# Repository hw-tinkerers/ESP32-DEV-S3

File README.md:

# ESP32-S3_Dev_Board
This development board is based on ESP32-S3 chipset which is aimed to solve the problem having to carry multiple tools to debug and capture data on RS485 and CAN bus.

<strong> Front view (Rendering)</strong>

<strong> Back view (Rendering)</strong>

The board is capable of operating in multiple modes.
1. With Firmware support (Still in making):
    1. CAN bus Decoder
    2. RS485 Decoder 

2. Standalone Hardware support:
    1. RS485 to USB converter
    2. USB to UART converter

3. Normal Development baord for ESP32-S3 Development.

<strong>The Board supports a wide variety of features.</strong>

| Interface    | Controller | Driver/Component |
| -------- | ------- | ------- |
| UART | on-chip | serial port |
GPIO | on-chip | gpio |
PINMUX | on-chip | pinmux |
USB-JTAG | on-chip | hardware interface
SPI Master | on-chip | spi
TWAI/CAN controller | on-chip | can
ADC | on-chip | adc
Timers | on-chip | counter
Watchdog | on-chip | watchdog	
TRNG | on-chip | entropy
MCPWM | on-chip | pwm 
PCNT | on-chip | qdec
GDMA | on-chip | dma
LEDC | on-chip | pwm
CAN trasnceiver | on-board | can
RS485 transceiver | on-board | serial-port
UART-to-USB | on-board | Hardare based

<strong>Development enviroinment support </strong>
The board is designed keeping open-source support in mind.
The main motive is to provide support on multiple development environments to cater to different people ranging from begginers to professionls. 

The supported platforms are listed below

1. Arduino IDE
2. ESP-IDF
3. Zephyr-RTOS

The guide on getting started on each platform is still in making. Stay tuned for further updates.

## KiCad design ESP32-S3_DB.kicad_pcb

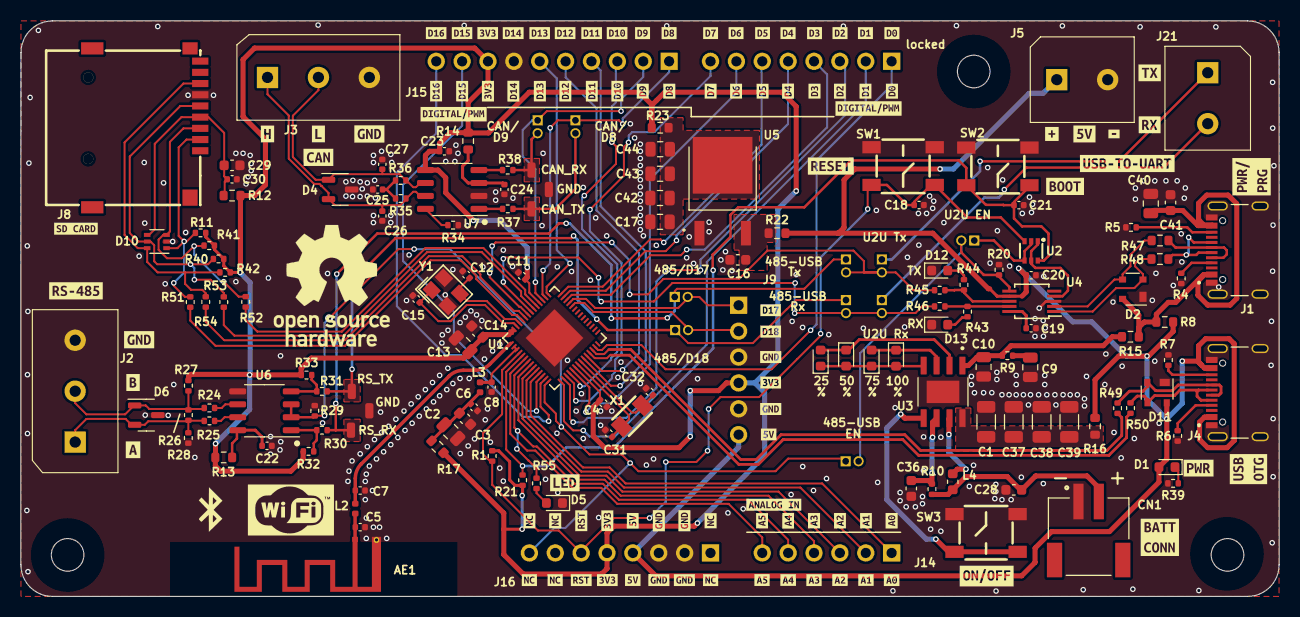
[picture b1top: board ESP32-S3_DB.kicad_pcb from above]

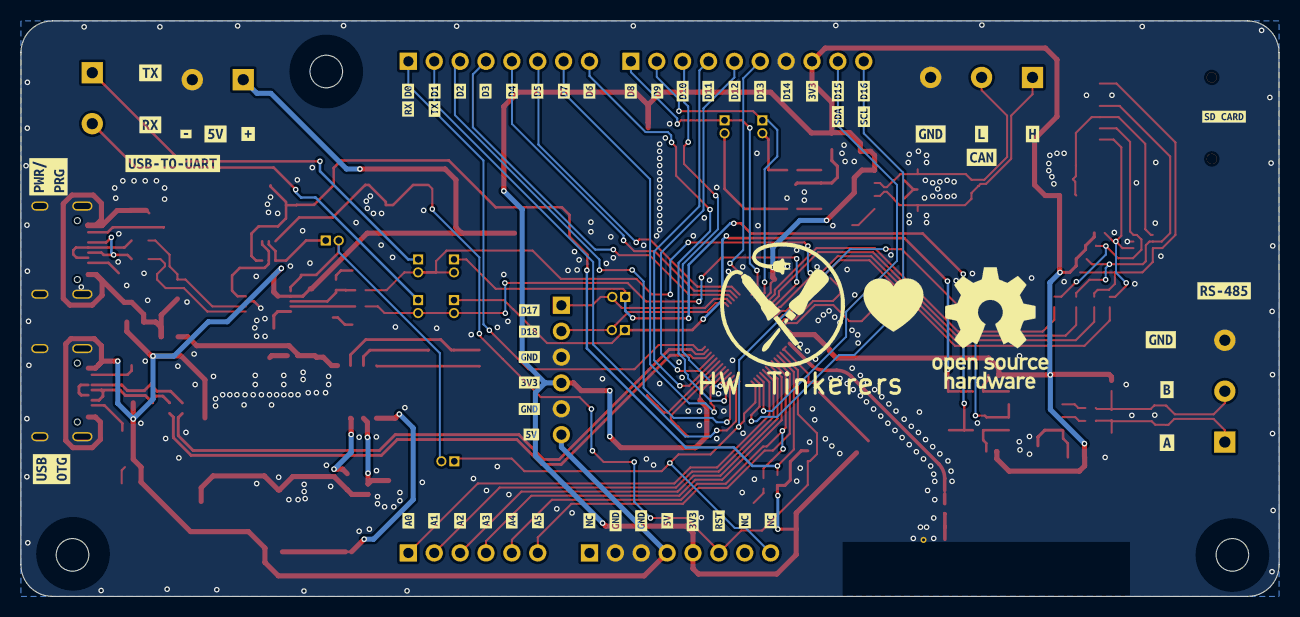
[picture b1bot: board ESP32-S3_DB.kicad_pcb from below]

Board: 4 copper layers, 123.5 x 56.5 mm, 310 parts (60 on the bottom side), 104 nets.

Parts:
AE1: Antenna_Shield; BLE_ANTENNA
C1, C37, C38, C39: 22uF; C_1206_3216Metric
C2, C9, C10, C13, C17, C40, C42, C43, C44: 10uF; C_0805_2012Metric
C3, C14, C16, C29, C41: 1uF; C_0603_1608Metric
C4, C6, C8, C11, C18, C19, C20, C21, C22, C23, C24, C30: 100nF; C_0402_1005Metric
C5, C7: 3.3pF; C_0402_1005Metric
C12, C15, C31, C32: 15pF; C_0402_1005Metric
C25, C26, C27: 10nF; C_0402_1005Metric
C28, C36: 22uF; C_0603_1608Metric
CN1: JST_Battery; JST_2mm
D1: BLUE; LED_0603_1608Metric
D2, D11: PRTR5V0U2X; SOT-143
D3, D5, D7, D8, D9, D12, D13: GREEN; LED_0603_1608Metric
D4: PESD2CAN; SOT-23-3
D6: SM712_C293966; SOT-23-3
D10: PESD3V3L5UY,115; SOT-363_SC-70-6
H1, H2, H3: MountingHole; MountingHole_3.2mm_M3
J1, J4: TYPE-C-31-M12_13; tyye_c_connector
J2: A - B; 3P_Screw_Terminal
J3: H - L; 3P_Screw_Terminal
J5: EXT_LOAD; 2P_Screw_Terminal
J6: R4_TX; PinHeader_1x02_P1.27mm_Vertical
J7: R4_RX; PinHeader_1x02_P1.27mm_Vertical
J8: Micro_SD_Card_Det1; TF-SMD_TF-012
J9, J14: Conn_01x06; PinHeader_1x06_P2.54mm_Vertical
J10: U2RS485_TX; PinHeader_1x02_P1.27mm_Vertical
J11: CAN_TX; PinHeader_1x02_P1.27mm_Vertical
J12: CAN_RX; PinHeader_1x02_P1.27mm_Vertical
J15: Conn_01x10; PinHeader_1x10_P2.54mm_Vertical
J16: Conn_01x08; PinHeader_1x08_P2.54mm_Vertical
J17: U2RS485_RX; PinHeader_1x02_P1.27mm_Vertical
J18: U2RS485_DE_~{RE}; PinHeader_1x02_P1.27mm_Vertical
J19: U2U_TX; PinHeader_1x02_P1.27mm_Vertical
J20: U2U_RX; PinHeader_1x02_P1.27mm_Vertical
J21: U2U; 2P_Screw_Terminal
J22: PROG_Default; PinHeader_1x02_P1.27mm_Vertical
L2, L3: 2.2nH; L_0402_1005Metric
L4: 1uH; L_0603_1608Metric
R1, R11, R21, R27, R28, R29, R40, R41, R42: 10k; R_0402_1005Metric
R4, R5, R6, R7, R20, R32, R33, R34: 5k1; R_0402_1005Metric
R8, R12, R13, R14, R15, R16, R17, R22, R23, R47, R48: 0E; R_0603_1608Metric
R9: 2E; R_0402_1005Metric
R10: 0.5E; R_0402_1005Metric
R24, R25, R30, R31, R37, R38, R45, R46, R49, R50, R51, R52, R53, R54: 10E; R_0402_1005Metric
R26: 120E; R_0402_1005Metric
R35: 59E; R_0402_1005Metric
R36: 59; R_0402_1005Metric
R39, R43, R44, R55: 500; R_0402_1005Metric
SW1: RESET; KEY-SMD_4P-L5.2-W5.2-P3.70-LS6.4
SW2: BOOT; KEY-SMD_4P-L5.2-W5.2-P3.70-LS6.4
SW3: ON/OFF; KEY-SMD_4P-L5.2-W5.2-P3.70-LS6.4
SYM1, SYM2: Logo_Open_Hardware_Large; OSHW-Logo_11.4x12mm_SilkScreen
TP1: RS_RX; Test_Pad_1.5mm
TP2: RS_TX; Test_Pad_1.5mm
TP3: CAN_TX; Test_Pad_1.5mm
TP4: CAN_RX; Test_Pad_1.5mm
TP5, TP6: GND; Test_Pad_1.5mm
U1: ESP32-S3FH4R2; QFN-56_L7.0-W7.0-P0.40-TL-EP4.0
U2: UMH3N; SC-70-6_L2.2-W1.3-P0.65-LS2.1-BR
U3: IP5306; ESOP-8
U4: CH340X; MSOP-10_3x3mm_P0.5mm
U5: LD1117DT33CTR; DPAK
U6: SP3071EEN-L/TR; SOP-8_3.9x4.9mm_P1.27mm
U7: ATA6561-GAQW-N; SOP-8_3.9x4.9mm_P1.27mm
X1: 32.768KHz; CRYSTAL-SMD_L3.2-W1.5
Y1: 40MHz; CRYSTAL-SMD_4P-L3.2-W2.5-BL
kibuzzard-65A92C15, kibuzzard-65A92C15#2, kibuzzard-65A92C15#3: G***; kibuzzard-65A92C15
kibuzzard-65A92C32, kibuzzard-65A92C32#2, kibuzzard-65A92C32#3: G***; kibuzzard-65A92C32
kibuzzard-65A92C44, kibuzzard-65A92C44#2, kibuzzard-65A92C44#3: G***; kibuzzard-65A92C44
kibuzzard-65A92C55, kibuzzard-65A92C55#2, kibuzzard-65A92C55#3: G***; kibuzzard-65A92C55
kibuzzard-65A92C85, kibuzzard-65A92C85#2, kibuzzard-65A92C85#3: G***; kibuzzard-65A92C85
kibuzzard-65A92C90, kibuzzard-65A92C90#2, kibuzzard-65A92C90#3: G***; kibuzzard-65A92C90
kibuzzard-65A92C99, kibuzzard-65A92C99#2, kibuzzard-65A92C99#3: G***; kibuzzard-65A92C99
kibuzzard-65A92CA3, kibuzzard-65A92CA3#2, kibuzzard-65A92CA3#3: G***; kibuzzard-65A92CA3
kibuzzard-65A92CE7, kibuzzard-65A92CE7#2: G***; kibuzzard-65A92CE7
kibuzzard-65A92E71, kibuzzard-65A92E71#2: G***; kibuzzard-65A92E71
kibuzzard-65A922D3, kibuzzard-65A922D3#2, kibuzzard-65A922D3#3: G***; kibuzzard-65A922D3
kibuzzard-65A922DA, kibuzzard-65A922DA#2, kibuzzard-65A922DA#3: G***; kibuzzard-65A922DA
kibuzzard-65A922E0, kibuzzard-65A922E0#2, kibuzzard-65A922E0#3: G***; kibuzzard-65A922E0
kibuzzard-65A922F7, kibuzzard-65A922F7#2, kibuzzard-65A922F7#3: G***; kibuzzard-65A922F7
kibuzzard-65A932A3, kibuzzard-65A932A3#2: G***; kibuzzard-65A932A3
kibuzzard-65A932F7, kibuzzard-65A932F7#2: G***; kibuzzard-65A932F7
kibuzzard-65A934AB, kibuzzard-65A934AB#2: G***; kibuzzard-65A934AB
kibuzzard-65A937AF, kibuzzard-65A937AF#2: G***; kibuzzard-65A937AF
kibuzzard-65A937DF: G***; kibuzzard-65A937DF
kibuzzard-65A9230D, kibuzzard-65A9230D#2, kibuzzard-65A9230D#3: G***; kibuzzard-65A9230D
kibuzzard-65A9357B: G***; kibuzzard-65A9357B
kibuzzard-65A9398B, kibuzzard-65A9398B#2: G***; kibuzzard-65A9398B
kibuzzard-65A92320, kibuzzard-65A92320#2, kibuzzard-65A92320#3: G***; kibuzzard-65A92320
kibuzzard-65A92621: G***; kibuzzard-65A92621
kibuzzard-65A93244, kibuzzard-65A93244#2: G***; kibuzzard-65A93244
kibuzzard-65A93266, kibuzzard-65A93266#2: G***; kibuzzard-65A93266
kibuzzard-65A93272, kibuzzard-65A93272#2: G***; kibuzzard-65A93272
kibuzzard-65A93313, kibuzzard-65A93313#2: G***; kibuzzard-65A93313
kibuzzard-65A93322, kibuzzard-65A93322#2: G***; kibuzzard-65A93322
kibuzzard-65A93334, kibuzzard-65A93334#2: G***; kibuzzard-65A93334
kibuzzard-65A93499, kibuzzard-65A93499#2: G***; kibuzzard-65A93499
kibuzzard-65A93960, kibuzzard-65A93960#2: G***; kibuzzard-65A93960
kibuzzard-65AB7A1C: G***; kibuzzard-65AB7A1C
kibuzzard-65AB7A3B, kibuzzard-65AB7A3B#2: G***; kibuzzard-65AB7A3B
kibuzzard-65AB7A4E, kibuzzard-65AB7A4E#2: G***; kibuzzard-65AB7A4E
kibuzzard-65AB7A5E, kibuzzard-65AB7A5E#2: G***; kibuzzard-65AB7A5E
kibuzzard-65AB7A9A, kibuzzard-65AB7A9A#2: G***; kibuzzard-65AB7A9A
kibuzzard-65AB7A9F: G***; kibuzzard-65AB7A9F
kibuzzard-65AB7A26, kibuzzard-65AB7A26#2: G***; kibuzzard-65AB7A26
kibuzzard-65AB7A41: G***; kibuzzard-65AB7A41
kibuzzard-65AB7A48: G***; kibuzzard-65AB7A48
kibuzzard-65AB7A58: G***; kibuzzard-65AB7A58
kibuzzard-65AB7A95: G***; kibuzzard-65AB7A95
kibuzzard-65AB7AA6, kibuzzard-65AB7AA6#2: G***; kibuzzard-65AB7AA6
kibuzzard-65AB7AAC: G***; kibuzzard-65AB7AAC
kibuzzard-65AB7AB4, kibuzzard-65AB7AB4#2: G***; kibuzzard-65AB7AB4
kibuzzard-65AB7ABA: G***; kibuzzard-65AB7ABA
kibuzzard-65AB7AC0, kibuzzard-65AB7AC0#2: G***; kibuzzard-65AB7AC0
kibuzzard-65AB7B50: G***; kibuzzard-65AB7B50
kibuzzard-65AB7B59, kibuzzard-65AB7B59#2: G***; kibuzzard-65AB7B59
kibuzzard-65AB7B60: G***; kibuzzard-65AB7B60
kibuzzard-65AB7B68, kibuzzard-65AB7B68#2: G***; kibuzzard-65AB7B68
kibuzzard-65AB72BB, kibuzzard-65AB72BB#2, kibuzzard-65AB72BB#3: G***; kibuzzard-65AB72BB
kibuzzard-65AB72CF, kibuzzard-65AB72CF#2, kibuzzard-65AB72CF#3: G***; kibuzzard-65AB72CF
kibuzzard-65AB99D3, kibuzzard-65AB99D3#2: G***; kibuzzard-65AB99D3
kibuzzard-65AB729F, kibuzzard-65AB729F#2, kibuzzard-65AB729F#3, kibuzzard-65AB729F#4, kibuzzard-65AB729F#5, kibuzzard-65AB729F#6: G***; kibuzzard-65AB729F
kibuzzard-65AB730A, kibuzzard-65AB730A#2, kibuzzard-65AB730A#3: G***; kibuzzard-65AB730A
kibuzzard-65AB731E, kibuzzard-65AB731E#2, kibuzzard-65AB731E#3, kibuzzard-65AB731E#4, kibuzzard-65AB731E#5, kibuzzard-65AB731E#6: G***; kibuzzard-65AB731E
kibuzzard-65AB7281, kibuzzard-65AB7281#2, kibuzzard-65AB7281#3: G***; kibuzzard-65AB7281
kibuzzard-65ABCD1E, kibuzzard-65ABCD1E#2: G***; kibuzzard-65ABCD1E
kibuzzard-65ABCD6A, kibuzzard-65ABCD6A#2: G***; kibuzzard-65ABCD6A
kibuzzard-65ABCD30, kibuzzard-65ABCD30#2: G***; kibuzzard-65ABCD30
kibuzzard-65ABCD42, kibuzzard-65ABCD42#2, kibuzzard-65ABCD42#3, kibuzzard-65ABCD42#4: G***; kibuzzard-65ABCD42
kibuzzard-65ABCD53, kibuzzard-65ABCD53#2: G***; kibuzzard-65ABCD53
kibuzzard-65ABCFED: G***; kibuzzard-65ABCFED
kibuzzard-65ABD001: G***; kibuzzard-65ABD001
kibuzzard-65ABD06D, kibuzzard-65ABD06D#2: G***; kibuzzard-65ABD06D
kibuzzard-65ABD087, kibuzzard-65ABD087#2: G***; kibuzzard-65ABD087
kibuzzard-65AD136A: G***; kibuzzard-65AD136A
kibuzzard-65AD1381: G***; kibuzzard-65AD1381
kibuzzard-65CC7CB6: G***; kibuzzard-65CC7CB6
kibuzzard-65CC7CF4: G***; kibuzzard-65CC7CF4
kibuzzard-65CDB80D: G***; kibuzzard-65CDB80D
kibuzzard-65CDB868: G***; kibuzzard-65CDB868
locked: Conn_01x08; PinHeader_1x08_P2.54mm_Vertical

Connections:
/3V3: C4.1, C11.1, C13.1, C14.1, C23.1, J9.4, J15.8, J16.5, R1.1, R11.2, R12.1, R13.2, R14.1, R17.1, R21.1, R23.2, R27.2, R32.2, R33.2, R40.2, R41.2, R42.2, U1.20 (VDD3P3_RTC), U1.46 (VDD3P3_CPU), U1.55 (VDDA), U1.56 (VDDA), U7.5 (VIO)
/5V: C20.2, D1.2 (A), D11.4 (VCC), J4.A4 (VBUS), J4.B4 (VBUS), J5.1, J9.6, J16.4, R8.2, R16.2, R22.1, U4.7 (VCC)
/485_TRANS_RX: J7.1, J17.1, R30.1, TP1.1
/485_TRANS_TX: J6.1, J10.1, R31.1, TP2.1
/BOOT: C21.2, R21.2, SW2.2, U1.5 (GPIO0), U2.6
/CAN TRANSCEIVER/RXD: R38.1, U7.4 (RXD)
/CAN TRANSCEIVER/TXD: R37.1, U7.1 (TXD)
/CAN_N: C27.2, D4.1, J3.2, R36.1, U7.6 (CANL)
/CAN_P: C26.1, D4.2, J3.1, R35.2, U7.7 (CANH)
/CAN_RXD/MTDO: J12.1, J15.2, U1.45 (MTDO)
/CAN_TRANS_RXD: J12.2, R38.2, TP4.1
/CAN_TRANS_TXD: J11.2, R37.2, TP3.1
/CAN_TXD/MTCK: J11.1, J15.1, U1.44 (MTCK)
/D+: D2.2 (I/O_1), R48.2, U4.1 (UD+)
/D-: D2.3 (I/O_2), R47.2, U4.2 (UD-)
/ESP32-S3/D+: R49.2, U1.26 (GPIO20)
/ESP32-S3/D-: R50.2, U1.25 (GPIO19)
/ESP32-S3/XTALN: C32.1, U1.22 (XTAL_32K_N), X1.2
/ESP32-S3/XTALP: C31.1, U1.21 (XTAL_32K_P), X1.1
/EXTERNAL CONNECTORS/CC1: J4.A5 (CC1), R6.1
/EXTERNAL CONNECTORS/CC2: J4.B5 (CC2), R7.1
/GPIO1: J14.6, U1.6 (GPIO1)
/GPIO2: J14.5, R55.2, U1.7 (GPIO2)
/GPIO3: J14.4, U1.8 (GPIO3)
/GPIO4: J14.3, U1.9 (GPIO4)
/GPIO5: J14.2, U1.10 (GPIO5)
/GPIO6: J14.1, U1.11 (GPIO6)
/GPIO7: J15.9, U1.12 (GPIO7)
/GPIO8: J15.10, U1.13 (GPIO8)
/GPIO10: U1.15 (GPIO10), locked.2
/GPIO11: U1.16 (GPIO11), locked.3
/GPIO12: U1.17 (GPIO12), locked.8
/GPIO13: J15.3, U1.18 (GPIO13)
/GPIO14: U1.19 (GPIO14), locked.7
/GPIO17: J15.4, U1.23 (GPIO17)
/GPIO18: J15.5, U1.24 (GPIO18)
/GPIO21: U1.27 (GPIO21), locked.1
/GPIO35: U1.40 (GPIO35), locked.4
/GPIO36: U1.41 (GPIO36), locked.5
/GPIO37: U1.42 (GPIO37), locked.6
/GPIO40: J15.6, U1.43 (GPIO38)
/INPUT POWER/CC1: J1.A5 (CC1), R4.1
/INPUT POWER/CC2: J1.B5 (CC2), R5.1
/INPUT POWER/LED1: D3.2 (A), D7.1 (K), U3.2 (LED1)
/INPUT POWER/LED2: D8.2 (A), D9.1 (K), U3.3 (LED2)
/INPUT POWER/LED3: D3.1 (K), D7.2 (A), D8.1 (K), D9.2 (A), U3.4 (LED3)
/INPUT POWER/VIN: C40.1, C41.1, D2.4 (VCC), J1.A4 (VBUS), J1.B4 (VBUS), R8.1, R15.1
/MCU_SL_CLK: D10.5 (L4), J8.5 (CLK), R40.1, R53.1
/MCU_SL_MISO: D10.6 (L5), J8.7 (DAT0), R42.1, R54.2
/MCU_SL_MOSI: D10.3 (L2), J8.3 (CMD), R41.1, R52.2
/OTG_D+: D11.2 (I/O_1), J4.A6 (D+), J4.B6 (D+), R49.1
/OTG_D-: D11.3 (I/O_2), J4.A7 (D-), J4.B7 (D-), R50.1
/R4_~RE_DE: J16.8, J18.1, R29.2, U1.14 (GPIO9), U6.2 (~RE), U6.3 (DE)
/RESET: C18.2, J16.6, R1.2, SW1.2, U1.4 (CHIP_PU), U2.3
/RS485_N: D6.2, J2.1, R25.2, R26.1, R28.2
/RS485_P: D6.1, J2.2, R24.2, R26.2, R27.1
/RS-485_RX/GPIO34: J7.2, J9.1, U1.39 (GPIO34)
/RS-485_TX/GPIO33: J6.2, J9.2, U1.38 (GPIO33)
/RS_485/RS-485_DI: R31.2, R33.1, U6.4 (DI)
/RS_485/RS-485_RO: R30.2, R32.1, U6.1 (RO)
/RS_485/RS_485_N: R25.1, U6.7 (B)
/RS_485/RS_485_P: R24.1, U6.6 (A)
/SD_CARD/VDD: C29.1, C30.1, D10.4 (L3), J8.4 (VDD), R12.2
/TNOW: J18.2, J22.2, R20.2, U4.6 (TNOW)
/U2U_CONN_RX: J20.1, J21.2
/U2U_CONN_TX: J19.1, J21.1
/U2U_RXD: J10.2, J20.2, R46.2, U1.49 (U0TXD)
/U2U_TXD: J17.2, J19.2, R45.2, U1.50 (U0RXD)
/USB-TO-UART/485_TX: R44.2, R45.1, U4.8 (TXD)
/USB-TO-UART/DTR: J22.1, U2.2, U2.4
/USB-TO-UART/RTS: U2.1, U2.5, U4.4 (~RTS)
/USB-TO-UART/V3: C19.2, U4.10 (V3)
/V_BAT: C28.1, CN1.2, L4.2, R10.2
/~MCU_SL_CS: D10.1 (L1), J8.2 (DAT3/CD), R11.1, R51.1
GND: AE1.2 (Shield), C1.2, C2.2, C3.2, C4.2, C5.2, C6.2, C7.2, C8.2, C9.2, C10.2, C11.2, C12.2, C13.2, C14.2, C15.2, C16.2, C17.2, C18.1, C19.1, C20.1, C21.1, C22.2, C23.2, C24.1, C25.1, C26.2, C27.1, C28.2, C29.2, C30.2, C31.2, C32.2, C36.2, C37.2, C38.2, C39.2, C40.2, C41.2, C42.2, C43.2, C44.2, CN1.1, D2.1 (GND), D4.3, D5.1 (K), D6.3, D10.2 (VN), D11.1 (GND), D12.1 (K), D13.1 (K), J1.A1 (GND), J1.B1 (GND), J1.S (SHIELD), J2.3, J3.3, J4.A1 (GND), J4.B1 (GND), J4.S (SHIELD), J5.2, J8.6 (VSS), J9.3, J9.5, J15.7, J16.2, J16.3, R4.2, R5.2, R6.2, R7.2, R20.1, R28.1, R29.1, R34.2, R39.2, SW1.1, SW2.1, SW3.2, TP5.1, TP6.1, U1.57 (GND), U3.9 (EP), U4.3 (GND), U5.1 (GND), U6.5 (GND), U7.2 (GND), Y1.2, Y1.4
unnamed: AE1.1 (A), C5.1, L2.1
unnamed: C2.1, C3.1, C6.1, L3.1, R17.2
unnamed: C8.1, L3.2, U1.2 (VDD3P3), U1.3 (VDD3P3)
unnamed: C9.1, R9.2
unnamed: C25.2, R35.1, R36.2
unnamed: D1.1 (K), R39.1
unnamed: D5.2 (A), R55.1
unnamed: D12.2 (A), R44.1
unnamed: D13.2 (A), R43.1
unnamed: J1.A6 (D+), J1.B6 (D+), R48.1
unnamed: J1.A7 (D-), J1.B7 (D-), R47.1
unnamed: R54.1, U1.51 (GPIO45)
unnamed: R51.2, U1.52 (GPIO46)
unnamed: C7.1, L2.2, U1.1 (LNA_IN)
unnamed: R52.1, U1.47 (MTDI)
unnamed: R53.2, U1.48 (MTMS)
unnamed: C12.1, U1.53 (XTAL_N), Y1.3
unnamed: C15.1, U1.54 (XTAL_P), Y1.1
unnamed: C36.1, R10.1, U3.6 (BAT)
unnamed: SW3.1, U3.5 (KEY)
unnamed: L4.1, U3.7 (SW)
unnamed: C10.1, R9.1, R15.2, U3.1 (VIN)
unnamed: C1.1, C37.1, C38.1, C39.1, R16.1, U3.8 (VOUT)
unnamed: R43.2, R46.1, U4.9 (RXD)
unnamed: C16.1, R22.2, U5.3 (VIN)
unnamed: C17.1, C42.1, C43.1, C44.1, R23.1, U5.2 (VOUT)
unnamed: C22.1, R13.1, U6.8 (VCC)
unnamed: R34.1, U7.8 (STBY)
unnamed: C24.2, R14.2, U7.3 (VCC)

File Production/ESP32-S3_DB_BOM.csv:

Designator,Footprint,Qty,Value,LCSC Part Number,MFR PN
"C1, C37, C38, C39",ESP32-S3_Dev_Board:C_1206_3216Metric,4,22uF,C12891,CL31A226KAHNNNE
"C2, C9, C10, C13, C17, C40, C42, C43, C44",ESP32-S3_Dev_Board:C_0805_2012Metric,9,10uF,C15850,CL21A106KAYNNNE
"C3, C14, C16, C29, C41",ESP32-S3_Dev_Board:C_0603_1608Metric,5,1uF,C14664,CC0603KRX5R8BB105
"C4, C6, C8, C11, C18, C19, C20, C21, C22, C23, C24, C30",ESP32-S3_Dev_Board:C_0402_1005Metric,12,100nF,C2173920,EMK107B7104KAHT
"C5, C7",ESP32-S3_Dev_Board:C_0402_1005Metric,2,3.3pF,C327287,CC0402BRNPO9BN3R3
"C12, C15, C31, C32",ESP32-S3_Dev_Board:C_0402_1005Metric,4,15pF,C326789,CC0402GRNPO8BN150
C25,ESP32-S3_Dev_Board:C_0402_1005Metric,1,10nF,C458948,MT15B103K250CT
"C28, C36",ESP32-S3_Dev_Board:C_0603_1608Metric,2,22uF,C2762594,CL10A226MO7JZNC
CN1,ESP32-S3_Dev_Board:JST_2mm,1,JST_Battery,C295747,S2B-PH-SM4-TB(LF)(SN) 
D1,ESP32-S3_Dev_Board:LED_0603_1608Metric,1,BLUE,C84266,NCD0603B1
"D2, D11",ESP32-S3_Dev_Board:SOT-143,2,PRTR5V0U2X,C2827688,PRTR5V0U2X
"D3, D5, D7, D8, D9, D12, D13",ESP32-S3_Dev_Board:LED_0603_1608Metric,7,GREEN,C84264,NCD0603C1
D4,ESP32-S3_Dev_Board:SOT-23-3,1,PESD2CAN,C284078,PESD2CAN
D6,ESP32-S3_Dev_Board:SOT-23-3,1,SM712_C293966,C293966,SM712
D10,ESP32-S3_Dev_Board:SOT-363_SC-70-6,1,"PESD3V3L5UY,115",C477992,"PESD3V3L5UY,115"
"J1, J4",ESP32-S3_Dev_Board:tyye_c_connector,2,TYPE-C-31-M12_13,C165948,TYPE-C-31-M-12
J8,ESP32-S3_Dev_Board:TF-SMD_TF-012,1,Micro_SD_Card_Det1,C5333937,TF-012-P9
"L2, L3",ESP32-S3_Dev_Board:L_0402_1005Metric,2,2.2nH,C76790,MLK1005S2N2ST000
L4,ESP32-S3_Dev_Board:L_0603_1608Metric,1,1uH,C576540,LQM18PN1R0MFHD
"R1, R11, R21, R27, R28, R29, R40, R41, R42",ESP32-S3_Dev_Board:R_0402_1005Metric,9,10k,C60490,RC0402FR-0710KL
"R36, R35",ESP32-S3_Dev_Board:R_0402_1005Metric,2,59E,C273340,RC0402FR-0759RL
"R4, R5, R6, R7, R20, R32, R33, R34",ESP32-S3_Dev_Board:R_0402_1005Metric,8,5k1,C105872,RC0402FR-075K1L
R9,ESP32-S3_Dev_Board:R_0402_1005Metric,1,2E,C477639,RC0402FR-072R1L
R10,ESP32-S3_Dev_Board:R_0402_1005Metric,1,0.5E,C346785,CSR0402FKR500
"R12, R13, R14, R15, R16, R17, R22, R23, R47, R48",ESP32-S3_Dev_Board:R_0603_1608Metric,10,0E,C95177,RC0603JR-070RL
"R24, R25, R30, R31, R37, R38, R45, R46, R49, R50, R51, R52, R53, R54",ESP32-S3_Dev_Board:R_0402_1005Metric,14,10E,C102753,RTT02100JTH
R26,ESP32-S3_Dev_Board:R_0402_1005Metric,1,120E,C114758,RC0402FR-07120RL
"R39, R43, R44, R55",ESP32-S3_Dev_Board:R_0402_1005Metric,4,500,C137970,RC0402FR-07499RL
SW1,ESP32-S3_Dev_Board:KEY-SMD_4P-L5.2-W5.2-P3.70-LS6.4,1,RESET,C92584,K2-1187SQ-A4SW-06
SW2,ESP32-S3_Dev_Board:KEY-SMD_4P-L5.2-W5.2-P3.70-LS6.4,1,BOOT,C92584,K2-1187SQ-A4SW-06
SW3,ESP32-S3_Dev_Board:KEY-SMD_4P-L5.2-W5.2-P3.70-LS6.4,1,ON/OFF,C92584,K2-1187SQ-A4SW-06
U1,ESP32-S3_Dev_Board:QFN-56_L7.0-W7.0-P0.40-TL-EP4.0,1,ESP32-S3FH4R2,C3013940,ESP32-S3FH4R2
U2,ESP32-S3_Dev_Board:SC-70-6_L2.2-W1.3-P0.65-LS2.1-BR,1,UMH3N,C62892,UMH3N
U3,ESP32-S3_Dev_Board:ESOP-8,1,IP5306,C181692,IP5306
U4,ESP32-S3_Dev_Board:MSOP-10_3x3mm_P0.5mm,1,CH340X,C3035748,CH340X
U5,ESP32-S3_Dev_Board:DPAK,1,LD1117DT33CTR ,C36395,LD1117DT33CTR
U6,ESP32-S3_Dev_Board:SOP-8_3.9x4.9mm_P1.27mm,1,SP3071EEN-L/TR,C28746,SP3071EEN-L/TR
U7,ESP32-S3_Dev_Board:SOP-8_3.9x4.9mm_P1.27mm,1,ATA6561-GAQW-N,C616016,ATA6561-GAQW-N
X1,ESP32-S3_Dev_Board:CRYSTAL-SMD_L3.2-W1.5,1,32.768KHz,C7206317,RN32768016
Y1,ESP32-S3_Dev_Board:CRYSTAL-SMD_4P-L3.2-W2.5-BL,1,40MHz,C2901712,SX3B40.000F1210F30

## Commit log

2023-08-22 Schematic file with Symbol library
2023-08-22 Started designed the schematics
    Placed passives for supply pins and antenna
2023-08-23 Added External Flash and Power sheets
    Added External Flash and Power sheets. Finished adding all the passives at their respective pins. Incorrect Pin number and signal corrected.
2023-09-04 Created Block arrangement and added USB C connector
2023-09-04 completed USB-C wiring and added flash
2023-09-06 Added USB-To-UART Converter
2023-09-12 Made USB-To-UART connections
2023-09-16 Added RS-485 Transceiver
2023-09-17 Minor UART corrections
2023-09-17 UART Tx and Rx correctly placed
2023-09-17 Completed RS-485 connections
2023-09-17 Added CAN Transceiver
2023-09-18 Added IP5306 for power path management
2023-09-19 Assigned UART port 2 for RS-485
2023-09-21 Added SD card interface
2023-09-23 Added SD card protection
2023-09-23 Added Female Headers
2023-09-24 Completed header connections
2023-09-24 Added 32.768KHz crystal for lower power usage
2023-09-27 Assigned PN and Footprint for C
2023-10-01 Some modifications
2023-10-01 Minor modifications
2023-10-09 Assigned footprints
2023-10-12 Screw Terminal FPs
2023-10-13 Added LNA_IN Passives
2023-10-14 Instigated PCB Design
2023-10-16 Arranged power section on PCB
2023-10-18 Added bulk Decoupling and arranged components
2023-10-20 Changed USB C footprint and arranged components
2023-10-22 Placed RS-485, CAN Transceiver and battery charger
2023-10-23 Placed ESP32-S3
2023-10-24 Placed all the components and added OSHW symbol
2023-10-25 Corrected schematic to PCB export error and warings and IP5306 and SD card section
2023-10-26 Changes CH340 schematic
2023-10-27 Corrected RS485 schematic
2023-10-27 Made minor changes in connectors sheet
2023-10-27 Added CAN Jumpers, changed jumper pitch to 1.27mm
2023-10-28 Changed GPIO headers to Arduino style
2023-10-30 Arranged IP5306, Added support for USB-To-RS485
2023-10-30 Arranged arduino headers as per the Uno R3 dimensions
2023-10-31 Minor changes in Arduino GPIO headers
2023-11-04 First draft of component layout
2023-11-05 Added 3D Models
2023-11-05 Added selection jumper sheet and USB-UART option for board
2023-11-27 Made aesthetic changes in Schematics
2023-11-28 Added mounting holes
2023-11-29 Made changes in schematics, changed hierarchical sheet color
2023-11-30 Instigated routing
2023-12-10 Started ESP routing
2023-12-23 Changed GPIO mapping
2023-12-23 Changed MCU pin mapping
2023-12-26 Completed routing for all GPIO pins
2023-12-26 Completed RS485 and CAN routing
2023-12-27 Completed routing for USB peripheral for CH340
2024-01-02 Removed readme
2024-01-17 Finished routing
2024-01-17 Changed UART0 port connections
2024-01-18 Changed GPIO39, 40 crossing and added GND vias near other vias
2024-01-20 Added GND vias along antenna track, cleared tracks underneath antenna track
2024-01-20 Added Arduino style SS for GPIO headers, Added BLE & Wi-Fi symbol
2024-01-21 Adjusted Wi-Fi and BLE logo, added SS for jumpers
2024-01-31 Updated Readme file
2024-01-31 Changed pin mapping for ESP
2024-01-31 Changed Readme
2024-02-10 Solved DRC errors and improved routing
2024-02-13 Added selection jumper block diagram and solved DRC errors
2024-02-14 Added HW-Tinkerers logo and supporting graphics
2024-02-15 Added GERBER files
2024-02-24 Added production files for JLC (BOM and CPL)
